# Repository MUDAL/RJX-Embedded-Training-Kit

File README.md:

# RJX Embedded Training Kit

## Overview  

Hardware training platform built around **STM32L431** with:
- **5 V input** and dual **3.3 V rails** (digital +3V3 and analog +3V3A)
- **Li-ion charger/power-path** + **fuel gauge**
- Sensors (I2C/SMBus + SPI), UI peripherals (LCD/7-seg/buzzer), and **CAN**

This repository contains the complete **KiCad 9** hardware design, PDFs/datasheets, and the STM32CubeMX pinout file. I have ensured that it is properly version-controlled by removing unnecessary KiCad artefacts/tool-specific outputs which can easily be re-generated by any user, and ensuring transition from the schematic design to PCB design and vice-versa without using netlists. The block diagram of the project is shown in the image below.   

---

## Repository layout

```text
.
├── LICENSE
├── README.md
├── images
│   └── rjx_training_kit.png
├── pinout
│   └── pinout.ioc
└── rjx_training_kit
    ├── Docs         (schematic PDF, datasheets, links)
    ├── Hardware     (KiCad project: schematics + PCB)
    ├── Libs         (project libraries)
    └── Outputs      (manufacturing files)
```

---

## Quick start

### View / edit hardware (KiCad 9)
1. Install **KiCad v9** (recommended).
2. Open the project:
   - `rjx_training_kit/Hardware/rjx_training_kit.kicad_pro`
3. Schematic sheets:
   - Top-level: `rjx_training_kit/Hardware/rjx_training_kit.kicad_sch`
   - Sub-sheets: `rjx_training_kit/Hardware/microcontroller.kicad_sch`, `rjx_training_kit/Hardware/peripherals.kicad_sch`
4. PCB layout:
   - `rjx_training_kit/Hardware/rjx_training_kit.kicad_pcb`

### View pin configuration (STM32CubeMX)
- Open `pinout/pinout.ioc` in **STM32CubeMX**.

---

## Documentation

### Schematic PDF
- `rjx_training_kit/Docs/rjx_training_kit.pdf`

### Component datasheets
Datasheets used by the design are stored in:
- `rjx_training_kit/Docs/`

### External links
External forum references and troubleshooting links are maintained here:
- [README.md](rjx_training_kit/Docs/README.md)  

---

## Checklist

- [x] Schematic capture  
- [ ] Board setup  
- [ ] Component placement and routing  
- [ ] DRC  
- [ ] Generate manufacturing outputs and BOM   
- [ ] Place an order for the board on PCBWay  
- [ ] Preliminary board tests  
- [ ] Create a basic user guide on how to get started with the board  

## License
GPL-3.0 (see `LICENSE`).

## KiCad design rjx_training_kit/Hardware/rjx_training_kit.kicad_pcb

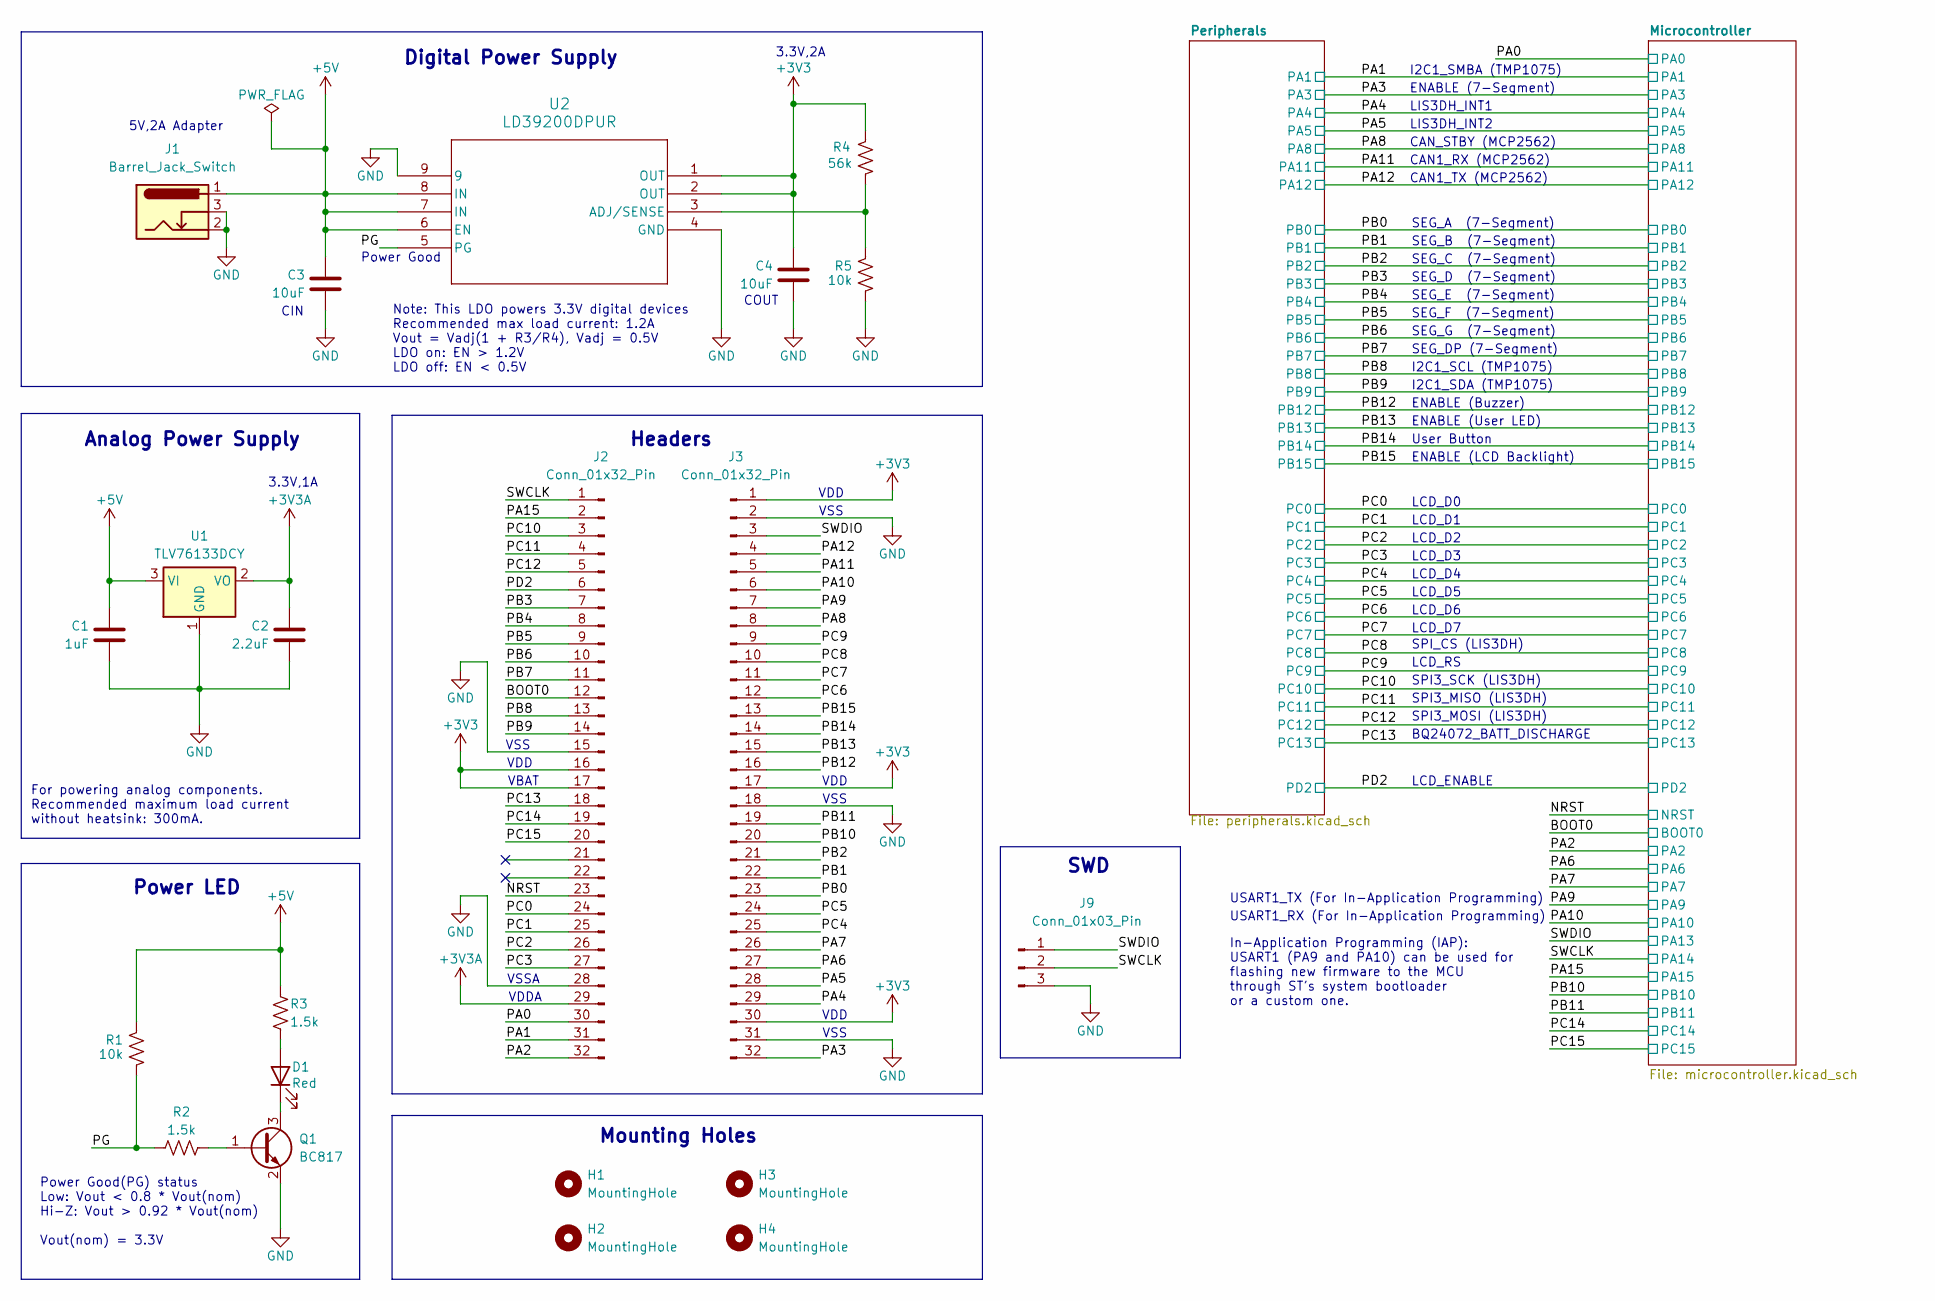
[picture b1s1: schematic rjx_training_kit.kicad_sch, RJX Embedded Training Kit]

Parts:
C1: 1uF; C_0603_1608Metric
C2: 2.2uF; C_0603_1608Metric
C3, C4: 10uF; C_0603_1608Metric
D1: Red; LED_0603_1608Metric
H1, H2, H3, H4: MountingHole; MountingHole_3mm
J1: Barrel_Jack_Switch; BarrelJack_Horizontal
J2, J3: Conn_01x32_Pin; PinHeader_1x32_P2.54mm_Vertical
J9: Conn_01x03_Pin; PinHeader_1x03_P2.54mm_Horizontal
Q1: BC817; SOT-23
R1, R5: 10k; R_0603_1608Metric
R2, R3: 1.5k; R_0603_1608Metric
R4: 56k; R_0603_1608Metric
U1: TLV76133DCY; SOT-223-3_TabPin2
U2: LD39200DPUR; DFN-8-1EP_4x4mm_P0.8mm_EP2.3x3.24mm

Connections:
+3V3: C4.1, J2.16, J2.17, J3.1, J3.17, J3.30, R4.2, U2.1 (OUT), U2.2 (OUT); also elsewhere on the board
+3V3A: C2.1, J2.29, U1.2 (VO); also elsewhere on the board
+5V: C1.1, C3.1, J1.1, R1.2, R3.1, U1.3 (VI), U2.6 (EN), U2.7 (IN), U2.8 (IN); also elsewhere on the board
/BOOT0: J2.12; also elsewhere on the board
/NRST: J2.23; also elsewhere on the board
/PA0: J2.30; also elsewhere on the board
/PA1: J2.31; also elsewhere on the board
/PA2: J2.32; also elsewhere on the board
/PA3: J3.32; also elsewhere on the board
/PA4: J3.29; also elsewhere on the board
/PA5: J3.28; also elsewhere on the board
/PA6: J3.27; also elsewhere on the board
/PA7: J3.26; also elsewhere on the board
/PA8: J3.8; also elsewhere on the board
/PA9: J3.7; also elsewhere on the board
/PA10: J3.6; also elsewhere on the board
/PA11: J3.5; also elsewhere on the board
/PA12: J3.4; also elsewhere on the board
/PA15: J2.2; also elsewhere on the board
/PB0: J3.23; also elsewhere on the board
/PB1: J3.22; also elsewhere on the board
/PB2: J3.21; also elsewhere on the board
/PB3: J2.7; also elsewhere on the board
/PB4: J2.8; also elsewhere on the board
/PB5: J2.9; also elsewhere on the board
/PB6: J2.10; also elsewhere on the board
/PB7: J2.11; also elsewhere on the board
/PB8: J2.13; also elsewhere on the board
/PB9: J2.14; also elsewhere on the board
/PB10: J3.20; also elsewhere on the board
/PB11: J3.19; also elsewhere on the board
/PB12: J3.16; also elsewhere on the board
/PB13: J3.15; also elsewhere on the board
/PB14: J3.14; also elsewhere on the board
/PB15: J3.13; also elsewhere on the board
/PC0: J2.24; also elsewhere on the board
/PC1: J2.25; also elsewhere on the board
/PC2: J2.26; also elsewhere on the board
/PC3: J2.27; also elsewhere on the board
/PC4: J3.25; also elsewhere on the board
/PC5: J3.24; also elsewhere on the board
/PC6: J3.12; also elsewhere on the board
/PC7: J3.11; also elsewhere on the board
/PC8: J3.10; also elsewhere on the board
/PC9: J3.9; also elsewhere on the board
/PC10: J2.3; also elsewhere on the board
/PC11: J2.4; also elsewhere on the board
/PC12: J2.5; also elsewhere on the board
/PC13: J2.18; also elsewhere on the board
/PC14: J2.19; also elsewhere on the board
/PC15: J2.20; also elsewhere on the board
/PD2: J2.6; also elsewhere on the board
/PG: R1.1, R2.1, U2.5 (PG)
/SWCLK: J2.1, J9.2; also elsewhere on the board
/SWDIO: J3.3, J9.1; also elsewhere on the board
GND: C1.2, C2.2, C3.2, C4.2, J1.2, J1.3, J2.15, J2.28, J3.2, J3.18, J3.31, J9.3, Q1.2 (E), R5.1, U1.1 (GND), U2.4 (GND), U2.9; also elsewhere on the board
unnamed: D1.2 (A), R3.2
unnamed: D1.1 (K), Q1.3 (C)
unnamed: Q1.1 (B), R2.2
unnamed: R4.1, R5.2, U2.3 (ADJ/SENSE)

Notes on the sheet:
SPI3_SCK (LIS3DH)
For powering analog components. Recommended maximum load current without heatsink: 300mA.
Mounting Holes
SEG_C (7-Segment)
COUT
VSS
Power Good(PG) status Low: Vout < 0.8 * Vout(nom) Hi-Z: Vout > 0.92 * Vout(nom) Vout(nom) = 3.3V
CAN_STBY (MCP2562)
I2C1_SDA (TMP1075)
ENABLE (7-Segment)
SEG_B (7-Segment)
Analog Power Supply
LIS3DH_INT2
ENABLE (Buzzer)
LCD_D0
VDDA
I2C1_SMBA (TMP1075)
3.3V,1A
LCD_D7
SWD
SPI3_MOSI (LIS3DH)
SEG_F (7-Segment)
LCD_D3
LCD_RS
LCD_D4
ENABLE (LCD Backlight)
LCD_D5
VDD
CIN
SEG_G (7-Segment)
User Button
Digital Power Supply
I2C1_SCL (TMP1075)
LCD_D1
5V,2A Adapter
SEG_DP (7-Segment)
LCD_D2
VSSA
3.3V,2A
USART1_TX (For In-Application Programming)

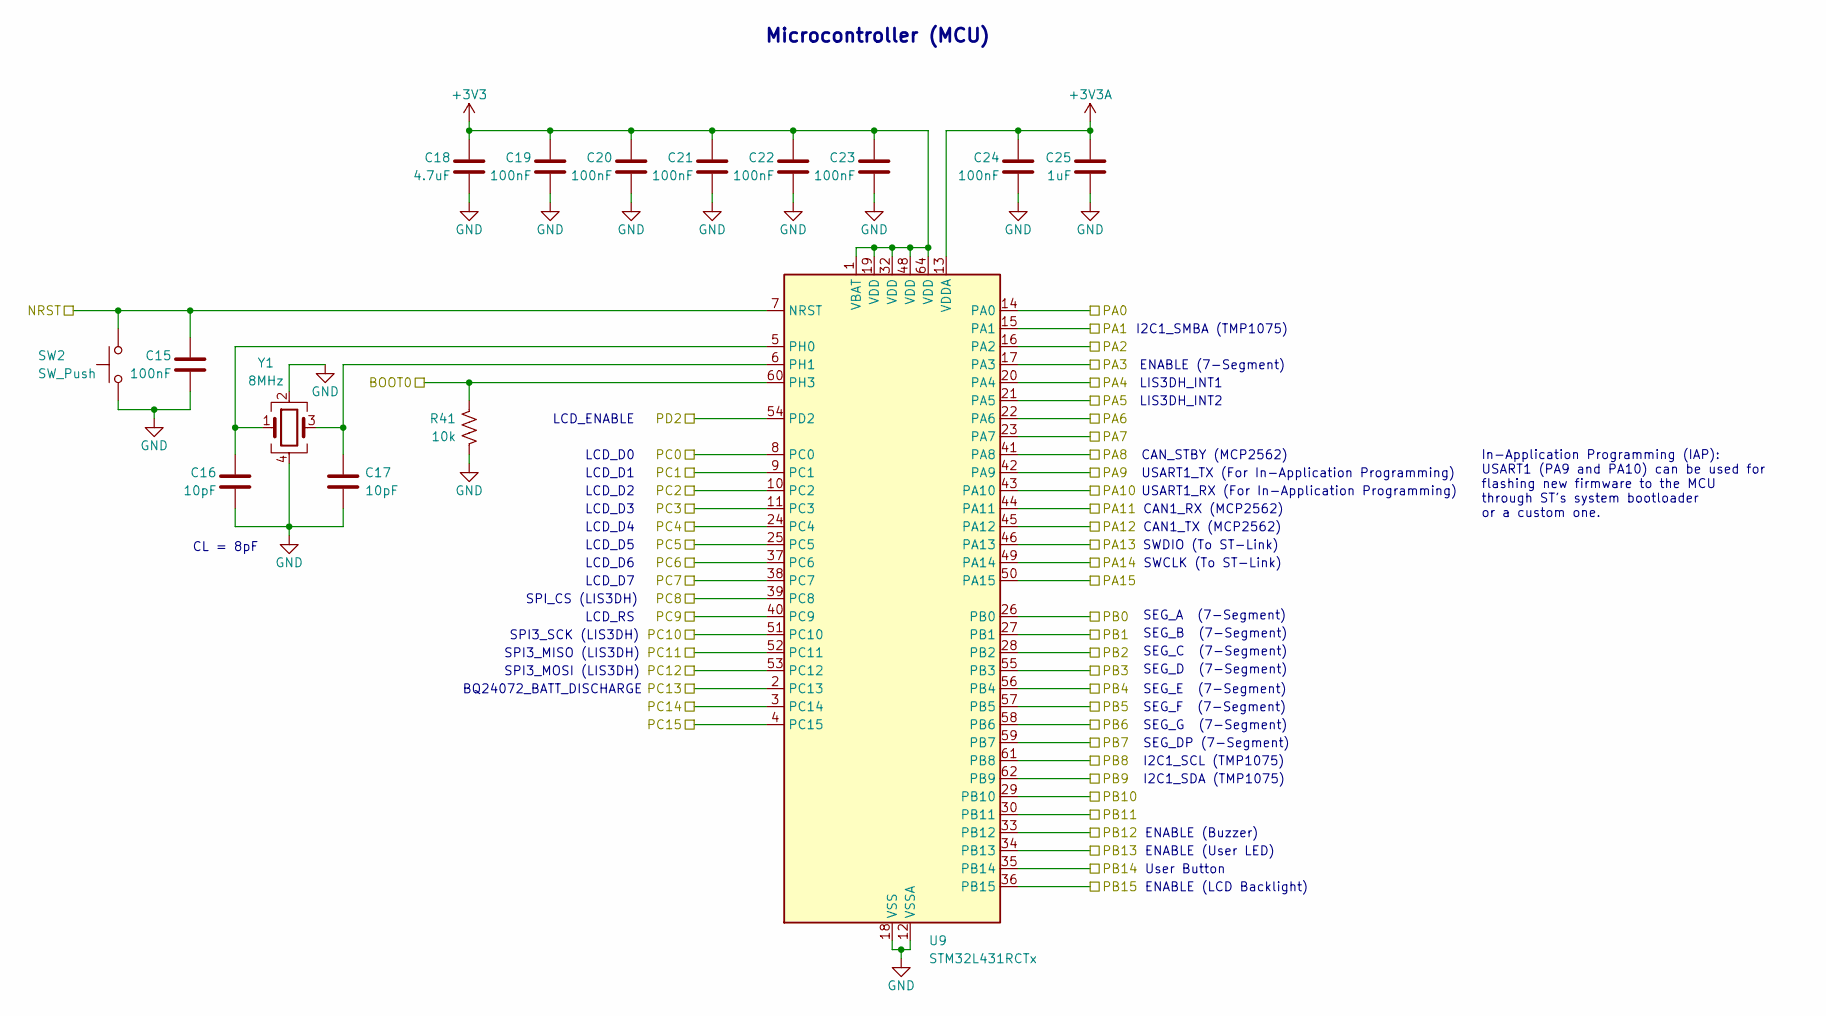
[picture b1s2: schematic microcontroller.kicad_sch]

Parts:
C15, C19, C20, C21, C22, C23, C24: 100nF; C_0603_1608Metric
C16, C17: 10pF; C_0603_1608Metric
C18: 4.7uF; C_0603_1608Metric
C25: 1uF; C_0603_1608Metric
R41: 10k; R_0603_1608Metric
SW2: SW_Push; SW_PUSH_6mm
U9: STM32L431RCTx; LQFP-64_10x10mm_P0.5mm
Y1: 8MHz; Crystal_SMD_3225-4Pin_3.2x2.5mm

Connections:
+3V3: C18.1, C19.1, C20.1, C21.1, C22.1, C23.1, U9.1 (VBAT), U9.19 (VDD), U9.32 (VDD), U9.48 (VDD), U9.64 (VDD); also elsewhere on the board
+3V3A: C24.1, C25.1, U9.13 (VDDA); also elsewhere on the board
/BOOT0: R41.1, U9.60 (PH3); also elsewhere on the board
/NRST: C15.1, SW2.2, U9.7 (NRST); also elsewhere on the board
/PA0: U9.14 (PA0); also elsewhere on the board
/PA1: U9.15 (PA1); also elsewhere on the board
/PA2: U9.16 (PA2); also elsewhere on the board
/PA3: U9.17 (PA3); also elsewhere on the board
/PA4: U9.20 (PA4); also elsewhere on the board
/PA5: U9.21 (PA5); also elsewhere on the board
/PA6: U9.22 (PA6); also elsewhere on the board
/PA7: U9.23 (PA7); also elsewhere on the board
/PA8: U9.41 (PA8); also elsewhere on the board
/PA9: U9.42 (PA9); also elsewhere on the board
/PA10: U9.43 (PA10); also elsewhere on the board
/PA11: U9.44 (PA11); also elsewhere on the board
/PA12: U9.45 (PA12); also elsewhere on the board
/PA15: U9.50 (PA15); also elsewhere on the board
/PB0: U9.26 (PB0); also elsewhere on the board
/PB1: U9.27 (PB1); also elsewhere on the board
/PB2: U9.28 (PB2); also elsewhere on the board
/PB3: U9.55 (PB3); also elsewhere on the board
/PB4: U9.56 (PB4); also elsewhere on the board
/PB5: U9.57 (PB5); also elsewhere on the board
/PB6: U9.58 (PB6); also elsewhere on the board
/PB7: U9.59 (PB7); also elsewhere on the board
/PB8: U9.61 (PB8); also elsewhere on the board
/PB9: U9.62 (PB9); also elsewhere on the board
/PB10: U9.29 (PB10); also elsewhere on the board
/PB11: U9.30 (PB11); also elsewhere on the board
/PB12: U9.33 (PB12); also elsewhere on the board
/PB13: U9.34 (PB13); also elsewhere on the board
/PB14: U9.35 (PB14); also elsewhere on the board
/PB15: U9.36 (PB15); also elsewhere on the board
/PC0: U9.8 (PC0); also elsewhere on the board
/PC1: U9.9 (PC1); also elsewhere on the board
/PC2: U9.10 (PC2); also elsewhere on the board
/PC3: U9.11 (PC3); also elsewhere on the board
/PC4: U9.24 (PC4); also elsewhere on the board
/PC5: U9.25 (PC5); also elsewhere on the board
/PC6: U9.37 (PC6); also elsewhere on the board
/PC7: U9.38 (PC7); also elsewhere on the board
/PC8: U9.39 (PC8); also elsewhere on the board
/PC9: U9.40 (PC9); also elsewhere on the board
/PC10: U9.51 (PC10); also elsewhere on the board
/PC11: U9.52 (PC11); also elsewhere on the board
/PC12: U9.53 (PC12); also elsewhere on the board
/PC13: U9.2 (PC13); also elsewhere on the board
/PC14: U9.3 (PC14); also elsewhere on the board
/PC15: U9.4 (PC15); also elsewhere on the board
/PD2: U9.54 (PD2); also elsewhere on the board
/SWCLK: U9.49 (PA14); also elsewhere on the board
/SWDIO: U9.46 (PA13); also elsewhere on the board
GND: C15.2, C16.2, C17.2, C18.2, C19.2, C20.2, C21.2, C22.2, C23.2, C24.2, C25.2, R41.2, SW2.1, U9.12 (VSSA), U9.18 (VSS), U9.31 (VSS), U9.47 (VSS), U9.63 (VSS), Y1.2, Y1.4; also elsewhere on the board
unnamed: C16.1, U9.5 (PH0), Y1.1
unnamed: C17.1, U9.6 (PH1), Y1.3

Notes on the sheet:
SPI3_MOSI (LIS3DH)
SWCLK (To ST-Link)
CAN1_RX (MCP2562)
SPI_CS (LIS3DH)
SEG_C (7-Segment)
ENABLE (User LED)
Microcontroller (MCU)
USART1_RX (For In-Application Programming)
LCD_ENABLE
USART1_TX (For In-Application Programming)
LIS3DH_INT2
ENABLE (Buzzer)
LCD_D5
ENABLE (LCD Backlight)
CAN1_TX (MCP2562)
SEG_B (7-Segment)
SPI3_SCK (LIS3DH)
LIS3DH_INT1
SWDIO (To ST-Link)
LCD_D0
LCD_D6
BQ24072_BATT_DISCHARGE
In-Application Programming (IAP): USART1 (PA9 and PA10) can be used for flashing new firmware to the MCU through ST's system bootloader or a custom one.
SEG_D (7-Segment)
SEG_DP (7-Segment)
ENABLE (7-Segment)
CL = 8pF
SEG_E (7-Segment)
LCD_RS
LCD_D4
LCD_D2
CAN_STBY (MCP2562)
I2C1_SCL (TMP1075)
I2C1_SMBA (TMP1075)
LCD_D3
SEG_G (7-Segment)
LCD_D7
User Button
SPI3_MISO (LIS3DH)
LCD_D1

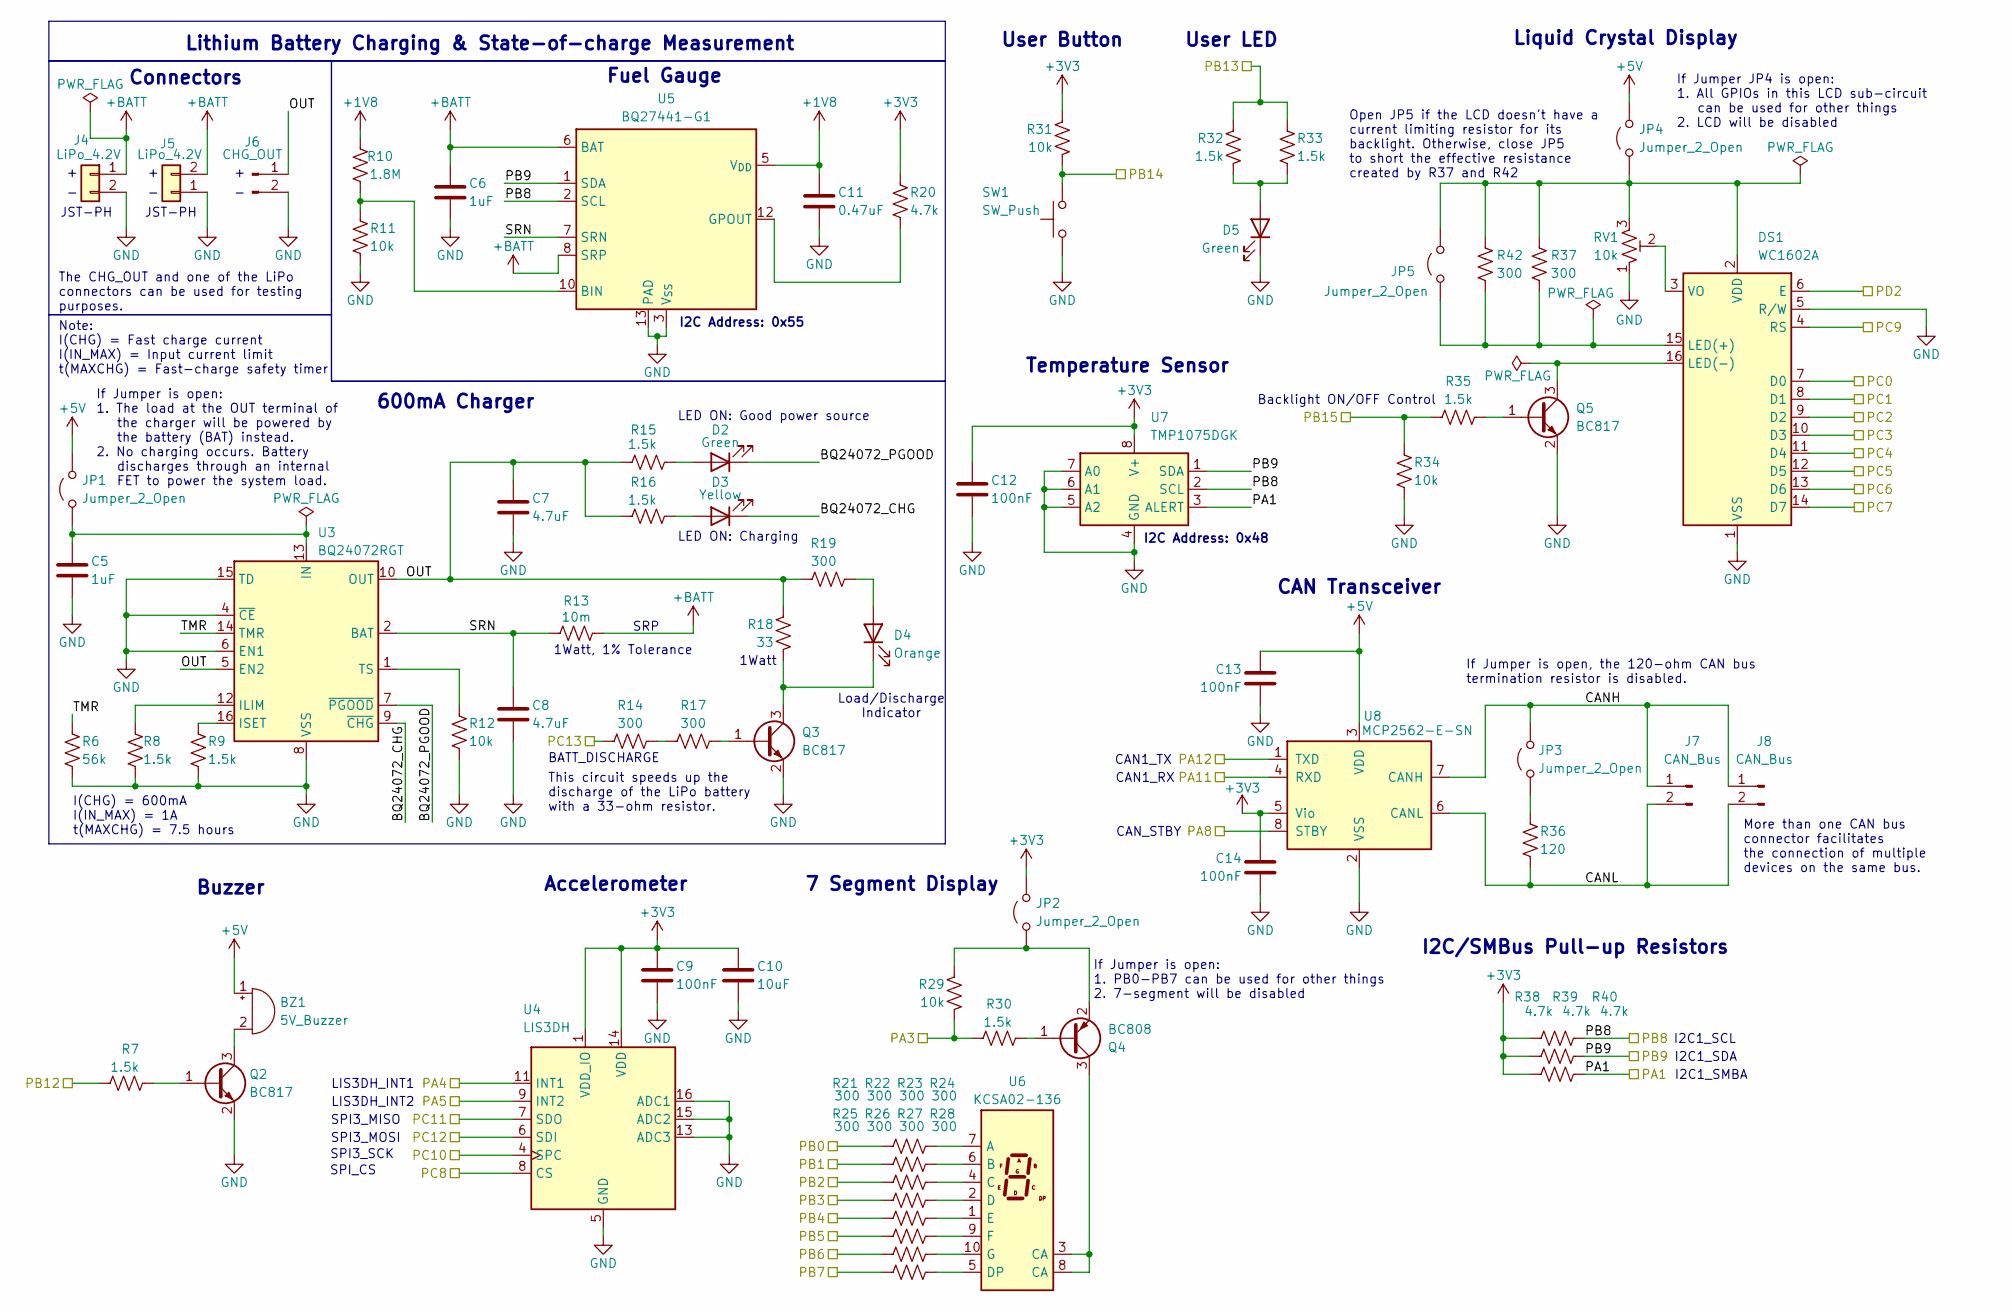
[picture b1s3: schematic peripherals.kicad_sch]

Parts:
BZ1: 5V_Buzzer; Buzzer_12x9.5RM7.6
C5, C6: 1uF; C_0603_1608Metric
C7, C8: 4.7uF; C_0603_1608Metric
C9, C12, C13, C14: 100nF; C_0603_1608Metric
C10: 10uF; C_0603_1608Metric
C11: 0.47uF; C_0603_1608Metric
D2, D5: Green; LED_0603_1608Metric
D3: Yellow; LED_0603_1608Metric
D4: Orange; LED_0603_1608Metric
DS1: WC1602A; PinSocket_1x16_P2.54mm_Vertical
J4, J5: LiPo_4.2V; JST_PH_S2B-PH-K_1x02_P2.00mm_Horizontal
J6: CHG_OUT; PinHeader_1x02_P2.54mm_Vertical
J7, J8: CAN_Bus; PinHeader_1x02_P2.54mm_Vertical
JP1, JP2, JP3, JP4, JP5: Jumper_2_Open; PinHeader_1x02_P2.54mm_Vertical
Q2, Q3, Q5: BC817; SOT-23
Q4: BC808; SOT-23
R6: 56k; R_0603_1608Metric
R7, R8, R9, R15, R16, R30, R32, R33, R35: 1.5k; R_0603_1608Metric
R10: 1.8M; R_0603_1608Metric
R11, R12, R29, R31, R34: 10k; R_0603_1608Metric
R13: 10m; R_2512_6332Metric
R14, R17, R19, R21, R22, R23, R24, R25, R26, R27, R28, R37, R42: 300; R_0603_1608Metric
R18: 33; R_2512_6332Metric
R20, R38, R39, R40: 4.7k; R_0603_1608Metric
R36: 120; R_0603_1608Metric
RV1: 10k; Potentiometer_Bourns_3296W_Vertical
SW1: SW_Push; SW_PUSH_6mm
U3: BQ24072RGT; VQFN-16-1EP_3x3mm_P0.5mm_EP1.6x1.6mm
U4: LIS3DH; LGA-16_3x3mm_P0.5mm_LayoutBorder3x5y
U5: BQ27441-G1; Texas_S-PDSO-N12
U6: KCSA02-136; KCSC02-136
U7: TMP1075DGK; VSSOP-8_3x3mm_P0.65mm
U8: MCP2562-E-SN; SOIC-8_3.9x4.9mm_P1.27mm

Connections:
+1V8: C11.1, R10.1, U5.5 (V_{DD})
+3V3: C9.1, C10.1, C12.1, C14.1, JP2.2 (B), R20.1, R31.1, R38.1, R39.1, R40.1, U4.1 (VDD_IO), U4.14 (VDD), U7.8 (V+), U8.5 (Vio); also elsewhere on the board
+5V: BZ1.1 (+), C13.1, JP1.2 (B), JP4.2 (B), U8.3 (VDD); also elsewhere on the board
+BATT: C6.1, J4.1, J5.2, R13.2, U5.6 (BAT), U5.8 (SRP)
/PA1: R40.2, U7.3 (ALERT); also elsewhere on the board
/PA3: R29.2, R30.1; also elsewhere on the board
/PA4: U4.11 (INT1); also elsewhere on the board
/PA5: U4.9 (INT2); also elsewhere on the board
/PA8: U8.8 (STBY); also elsewhere on the board
/PA11: U8.4 (RXD); also elsewhere on the board
/PA12: U8.1 (TXD); also elsewhere on the board
/PB0: R21.1; also elsewhere on the board
/PB1: R22.1; also elsewhere on the board
/PB2: R23.1; also elsewhere on the board
/PB3: R24.1; also elsewhere on the board
/PB4: R25.1; also elsewhere on the board
/PB5: R26.1; also elsewhere on the board
/PB6: R27.1; also elsewhere on the board
/PB7: R28.1; also elsewhere on the board
/PB8: R38.2, U5.2 (SCL), U7.2 (SCL); also elsewhere on the board
/PB9: R39.2, U5.1 (SDA), U7.1 (SDA); also elsewhere on the board
/PB12: R7.1; also elsewhere on the board
/PB13: R32.1, R33.1; also elsewhere on the board
/PB14: R31.2, SW1.2; also elsewhere on the board
/PB15: R34.1, R35.1; also elsewhere on the board
/PC0: DS1.7 (D0); also elsewhere on the board
/PC1: DS1.8 (D1); also elsewhere on the board
/PC2: DS1.9 (D2); also elsewhere on the board
/PC3: DS1.10 (D3); also elsewhere on the board
/PC4: DS1.11 (D4); also elsewhere on the board
/PC5: DS1.12 (D5); also elsewhere on the board
/PC6: DS1.13 (D6); also elsewhere on the board
/PC7: DS1.14 (D7); also elsewhere on the board
/PC8: U4.8 (CS); also elsewhere on the board
/PC9: DS1.4 (RS); also elsewhere on the board
/PC10: U4.4 (SPC); also elsewhere on the board
/PC11: U4.7 (SDO); also elsewhere on the board
/PC12: U4.6 (SDI); also elsewhere on the board
/PC13: R14.1; also elsewhere on the board
/PD2: DS1.6 (E); also elsewhere on the board
/Peripherals/BQ24072_CHG: D3.1 (K), U3.9 (~CHG)
/Peripherals/BQ24072_PGOOD: D2.1 (K), U3.7 (~PGOOD)
/Peripherals/CANH: J7.1, J8.1, JP3.2 (B), U8.7 (CANH)
/Peripherals/CANL: J7.2, J8.2, R36.2, U8.6 (CANL)
/Peripherals/OUT: C7.1, J6.1, R15.1, R16.1, R18.1, R19.1, U3.5 (EN2), U3.10 (OUT), U3.11 (OUT)
/Peripherals/SRN: C8.1, R13.1, U3.2 (BAT), U3.3 (BAT), U5.7 (SRN)
/Peripherals/TMR: R6.1, U3.14 (TMR)
GND: C5.2, C6.2, C7.2, C8.2, C9.2, C10.2, C11.2, C12.2, C13.2, C14.2, D5.1 (K), DS1.1 (VSS), DS1.5 (R/W), J4.2, J5.1, J6.2, Q2.2 (E), Q3.2 (E), Q5.2 (E), R6.2, R8.2, R9.2, R11.2, R12.2, R34.2, RV1.1, SW1.1, U3.4 (~CE), U3.6 (EN1), U3.8 (VSS), U3.15 (TD), U3.17 (VSS), U4.5 (GND), U4.10 (GND), U4.12 (GND), U4.13 (ADC3), U4.15 (ADC2), U4.16 (ADC1), U5.3 (V_{SS}), U5.13 (PAD), U7.4 (GND), U7.5 (A2), U7.6 (A1), U7.7 (A0), U8.2 (VSS); also elsewhere on the board
unnamed: BZ1.2 (-), Q2.3 (C)
unnamed: D2.2 (A), R15.2
unnamed: D3.2 (A), R16.2
unnamed: D4.2 (A), R19.2
unnamed: D4.1 (K), Q3.3 (C), R18.2
unnamed: D5.2 (A), R32.2, R33.2
unnamed: DS1.15 (LED(+)), JP5.1 (A), R37.1, R42.1
unnamed: DS1.16 (LED(-)), Q5.3 (C)
unnamed: DS1.2 (VDD), JP4.1 (A), JP5.2 (B), R37.2, R42.2, RV1.3
unnamed: DS1.3 (VO), RV1.2
unnamed: C5.1, JP1.1 (A), U3.13 (IN)
unnamed: JP2.1 (A), Q4.2 (E), R29.1
unnamed: JP3.1 (A), R36.1
unnamed: Q2.1 (B), R7.2
unnamed: Q3.1 (B), R17.2
unnamed: Q4.1 (B), R30.2
unnamed: Q4.3 (C), U6.3 (CA), U6.8 (CA)
unnamed: Q5.1 (B), R35.2
unnamed: R14.2, R17.1
unnamed: R8.1, U3.12 (ILIM)
unnamed: R9.1, U3.16 (ISET)
unnamed: R12.1, U3.1 (TS)
unnamed: R10.2, R11.1, U5.10 (BIN)
unnamed: R20.2, U5.12 (GPOUT)
unnamed: R21.2, U6.7 (A)
unnamed: R22.2, U6.6 (B)
unnamed: R23.2, U6.4 (C)
unnamed: R24.2, U6.2 (D)
unnamed: R28.2, U6.5 (DP)
unnamed: R25.2, U6.1 (E)
unnamed: R26.2, U6.9 (F)
unnamed: R27.2, U6.10 (G)

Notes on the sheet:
If Jumper JP4 is open: 1. All GPIOs in this LCD sub-circuit can be used for other things 2. LCD will be disabled
SPI3_MISO
Liquid Crystal Display
If Jumper is open: 1. The load at the OUT terminal of the charger will be powered by the battery (BAT) instead. 2. No charging occurs. Battery discharges through an internal FET to power the system load.
I2C Address: 0x55
CAN1_TX
SPI3_SCK
User Button
I2C/SMBus Pull-up Resistors
JST-PH
I2C Address: 0x48
CAN_STBY
Lithium Battery Charging & State-of-charge Measurement
This circuit speeds up the discharge of the LiPo battery with a 33-ohm resistor.
Note: I(CHG) = Fast charge current I(IN_MAX) = Input current limit t(MAXCHG) = Fast-charge safety timer
600mA Charger
Buzzer
I2C1_SMBA
User LED
LED ON: Good power source
I2C1_SCL
LIS3DH_INT1
I2C1_SDA
SRP
Load/Discharge Indicator
Temperature Sensor
SPI3_MOSI
SPI_CS
I(CHG) = 600mA I(IN_MAX) = 1A t(MAXCHG) = 7.5 hours
More than one CAN bus connector facilitates the connection of multiple devices on the same bus.
Open JP5 if the LCD doesn't have a current limiting resistor for its backlight. Otherwise, close JP5 to short the effective resistance created by R37 and R42
CAN Transceiver
Accelerometer
Connectors
1Watt, 1% Tolerance
7 Segment Display
Backlight ON/OFF Control
If Jumper is open, the 120-ohm CAN bus termination resistor is disabled.
1Watt
LED ON: Charging

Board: 4 copper layers, 110 parts (0 on the bottom side), 103 nets, no tracks yet.

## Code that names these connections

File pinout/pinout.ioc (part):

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Mcu.Name=STM32L431R(B-C)Tx
Mcu.Package=LQFP64
Mcu.UserName=STM32L431RCTx
PA1.Mode=SMBus-Alert-mode
PA1.Signal=I2C1_SMBA
PA10.Mode=Asynchronous
PA10.Signal=USART1_RX
PA11.Mode=CAN_Activate
PA11.Signal=CAN1_RX
PA12.Mode=CAN_Activate
PA12.Signal=CAN1_TX
PA13\ (JTMS-SWDIO).Mode=Serial_Wire
PA13\ (JTMS-SWDIO).Signal=SYS_JTMS-SWDIO
PA14\ (JTCK-SWCLK).Mode=Serial_Wire
PA14\ (JTCK-SWCLK).Signal=SYS_JTCK-SWCLK
PA15\ (JTDI).Mode=Asynchronous
PA15\ (JTDI).Signal=USART2_RX
PA2.Mode=Asynchronous
PA2.Signal=USART2_TX
PA3.GPIOParameters=GPIO_Label
PA3.GPIO_Label=SEGMENT_ENABLE
PA3.Signal=GPIO_Output
PA4.GPIOParameters=GPIO_Label
PA4.GPIO_Label=LIS3DH_INT1
PA4.Signal=GPIO_Input
PA5.GPIOParameters=GPIO_Label
PA5.GPIO_Label=LIS3DH_INT2
PA5.Signal=GPIO_Input
PA8.GPIOParameters=GPIO_Label
PA8.GPIO_Label=CAN_STBY
PA8.Signal=GPIO_Output
PA9.Mode=Asynchronous
PA9.Signal=USART1_TX
PB0.GPIOParameters=GPIO_Label
PB0.GPIO_Label=SEG_A
PB0.Signal=GPIO_Output
PB1.GPIOParameters=GPIO_Label
PB1.GPIO_Label=SEG_B
PB1.Signal=GPIO_Output
PB10.Mode=I2C
PB10.Signal=I2C2_SCL
PB11.Mode=I2C
PB11.Signal=I2C2_SDA
PB12.GPIOParameters=GPIO_Label
PB12.GPIO_Label=BUZZER
PB12.Signal=GPIO_Output
PB13.GPIOParameters=GPIO_Label
PB13.GPIO_Label=USER_LED
PB13.Signal=GPIO_Output
PB14.GPIOParameters=GPIO_Label
PB14.GPIO_Label=USER_BUTTON
PB14.Signal=GPIO_Input
PB15.GPIOParameters=GPIO_Label
PB15.GPIO_Label=LCD_BACKLIGHT
PB15.Signal=GPIO_Output
PB2.GPIOParameters=GPIO_Label
PB2.GPIO_Label=SEG_C
PB2.Signal=GPIO_Output
PB3\ (JTDO-TRACESWO).GPIOParameters=GPIO_Label
PB3\ (JTDO-TRACESWO).GPIO_Label=SEG_D
PB3\ (JTDO-TRACESWO).Signal=GPIO_Output
PB4\ (NJTRST).GPIOParameters=GPIO_Label
PB4\ (NJTRST).GPIO_Label=SEG_E
PB4\ (NJTRST).Signal=GPIO_Output
PB5.GPIOParameters=GPIO_Label
PB5.GPIO_Label=SEG_F
PB5.Signal=GPIO_Output
PB6.GPIOParameters=GPIO_Label
PB6.GPIO_Label=SEG_G
PB6.Signal=GPIO_Output
PB7.GPIOParameters=GPIO_Label
PB7.GPIO_Label=SEG_DP
PB7.Signal=GPIO_Output
PB8.Mode=SMBus-Alert-mode
PB8.Signal=I2C1_SCL
PB9.Mode=SMBus-Alert-mode
PB9.Signal=I2C1_SDA
PC0.GPIOParameters=GPIO_Label
PC0.GPIO_Label=LCD_D0
PC0.Signal=GPIO_Output
PC1.GPIOParameters=GPIO_Label
PC1.GPIO_Label=LCD_D1
PC1.Signal=GPIO_Output
PC10.Mode=Full_Duplex_Master
PC10.Signal=SPI3_SCK
PC11.Mode=Full_Duplex_Master
PC11.Signal=SPI3_MISO
PC12.Mode=Full_Duplex_Master
PC12.Signal=SPI3_MOSI
PC13.GPIOParameters=GPIO_Label
PC13.GPIO_Label=BATTERY_DISCHARGE
PC13.Signal=GPIO_Output
PC2.GPIOParameters=GPIO_Label
PC2.GPIO_Label=LCD_D2
PC2.Signal=GPIO_Output
PC3.GPIOParameters=GPIO_Label
PC3.GPIO_Label=LCD_D3
PC3.Signal=GPIO_Output
PC4.GPIOParameters=GPIO_Label
PC4.GPIO_Label=LCD_D4
PC4.Signal=GPIO_Output
PC5.GPIOParameters=GPIO_Label
PC5.GPIO_Label=LCD_D5
PC5.Signal=GPIO_Output
PC6.GPIOParameters=GPIO_Label
PC6.GPIO_Label=LCD_D6
PC6.Signal=GPIO_Output
PC7.GPIOParameters=GPIO_Label
PC7.GPIO_Label=LCD_D7
PC7.Signal=GPIO_Output
PC8.GPIOParameters=GPIO_Label
PC8.GPIO_Label=SPI_CS
PC8.Signal=GPIO_Output
PC9.GPIOParameters=GPIO_Label
PC9.GPIO_Label=LCD_RS
PC9.Signal=GPIO_Output
PD2.GPIOParameters=GPIO_Label
PD2.GPIO_Label=LCD_EN
PD2.Signal=GPIO_Output
PH0-OSC_IN\ (PH0).Mode=HSE-External-Oscillator
PH0-OSC_IN\ (PH0).Signal=RCC_OSC_IN
PH1-OSC_OUT\ (PH1).Mode=HSE-External-Oscillator
PH1-OSC_OUT\ (PH1).Signal=RCC_OSC_OUT
RCC.HSE_VALUE=8000000
board=custom

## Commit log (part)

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2026-03-04 [RJX]: New project structure
2026-03-04 [RJX]: Removed the reference_docs directory
2026-03-05 [RJX]: Label for PA0 no longer needed
2026-03-05 [RJX]: Moved links to a separate directory in order to improve the repository's structure
2026-03-05 [RJX]: Updated README
2026-03-05 [RJX]: Removed SRP label to eliminate annoying KiCad warning. This warning shows up because the SRP label is connected to +BATT.
2026-03-05 [RJX]: Schematic PDF update
2026-03-05 [RJX]: Changed the dates on the title blocks of all schematics
2026-03-06 [RJX]: Custom LD39200 footprint no longer required. Therefore, footprint table is unnecessary.
2026-03-06 [RJX]: Initial footprint assignment. This is subject to further review and analysis.
2026-03-06 [RJX]: Updated README.md. Additional markdown files containing information about BOM development and project research stages have been included in the repo.
2026-03-06 [RJX]: Added inner markdown files
2026-03-06 [RJX]: Minor fix applied to the body of the repository layout
2026-03-06 [RJX]: Inner markdown files now clickable.
2026-03-06 Rename links.md to Links.md
2026-03-09 [RJX]: Reference manual and generic routing guidelines
2026-03-11 [RJX]: Commenced parts research
2026-03-12 [RJX]: Added datasheet for crystal resonator
2026-03-12 [RJX]: Updated load capacitance values
2026-03-12 [RJX]: Updated on components research
2026-03-12 [RJX]: Schematic update
2026-03-16 [RJX]: Selected and verified most component footprints. Next task is to properly size the power resistors.
2026-03-19 [RJX]: Replaced the vertical footprint for the JST connector with a horizontal one.
2026-05-21 [RJX]: Removed BOM Checklist and Layout Reference Manual
2026-05-21 [RJX]: Initial netlist and commencement of PCB layout
2026-05-21 [RJX]: Schematic, Netlist, and PCB update. Replaced 2-pin crystal with 4-pin passive crystal.
2026-05-21 [RJX]: Deleted the Third_Party directory and kept all 3rd party libraries in the Libs directory for simplicity.
2026-05-21 [RJX]: Deleted netlist because it is poor for version control. The PCB is directly updated from the schematic instead of relying on netlists.
2026-05-31 [RJX]: Updated project layout
2026-05-31 [RJX]: Added image of the project's architecture/block diagram.
2026-05-31 [RJX]: Provided additional information about the project and centered the block diagram for visual clarity.
2026-06-07 [RJX]: Added checklist for the project.
2026-06-07 [RJX]: Corrected spelling error.
2026-06-09 [RJX]: Board setup + place and route in progress.
2026-06-09 [RJX]: Updated schematic by adding dedicated 3-pin connector for SWD.
2026-06-09 [RJX]: Schematic update with 3-pin SWD connector.
2026-06-09 [RJX]: Component placement in progress.
2026-06-10 [RJX]: Modified the schematic to account for different types of LCDs (some have current-limiting resistors, others don't). Also changed Links.md to an inner README.md file
2026-06-12 [RJX]: Small note on I2C addresses.
2026-06-21 [RJX]: Component placement nearing completion. Though it's still subject to change after DRC is performed
